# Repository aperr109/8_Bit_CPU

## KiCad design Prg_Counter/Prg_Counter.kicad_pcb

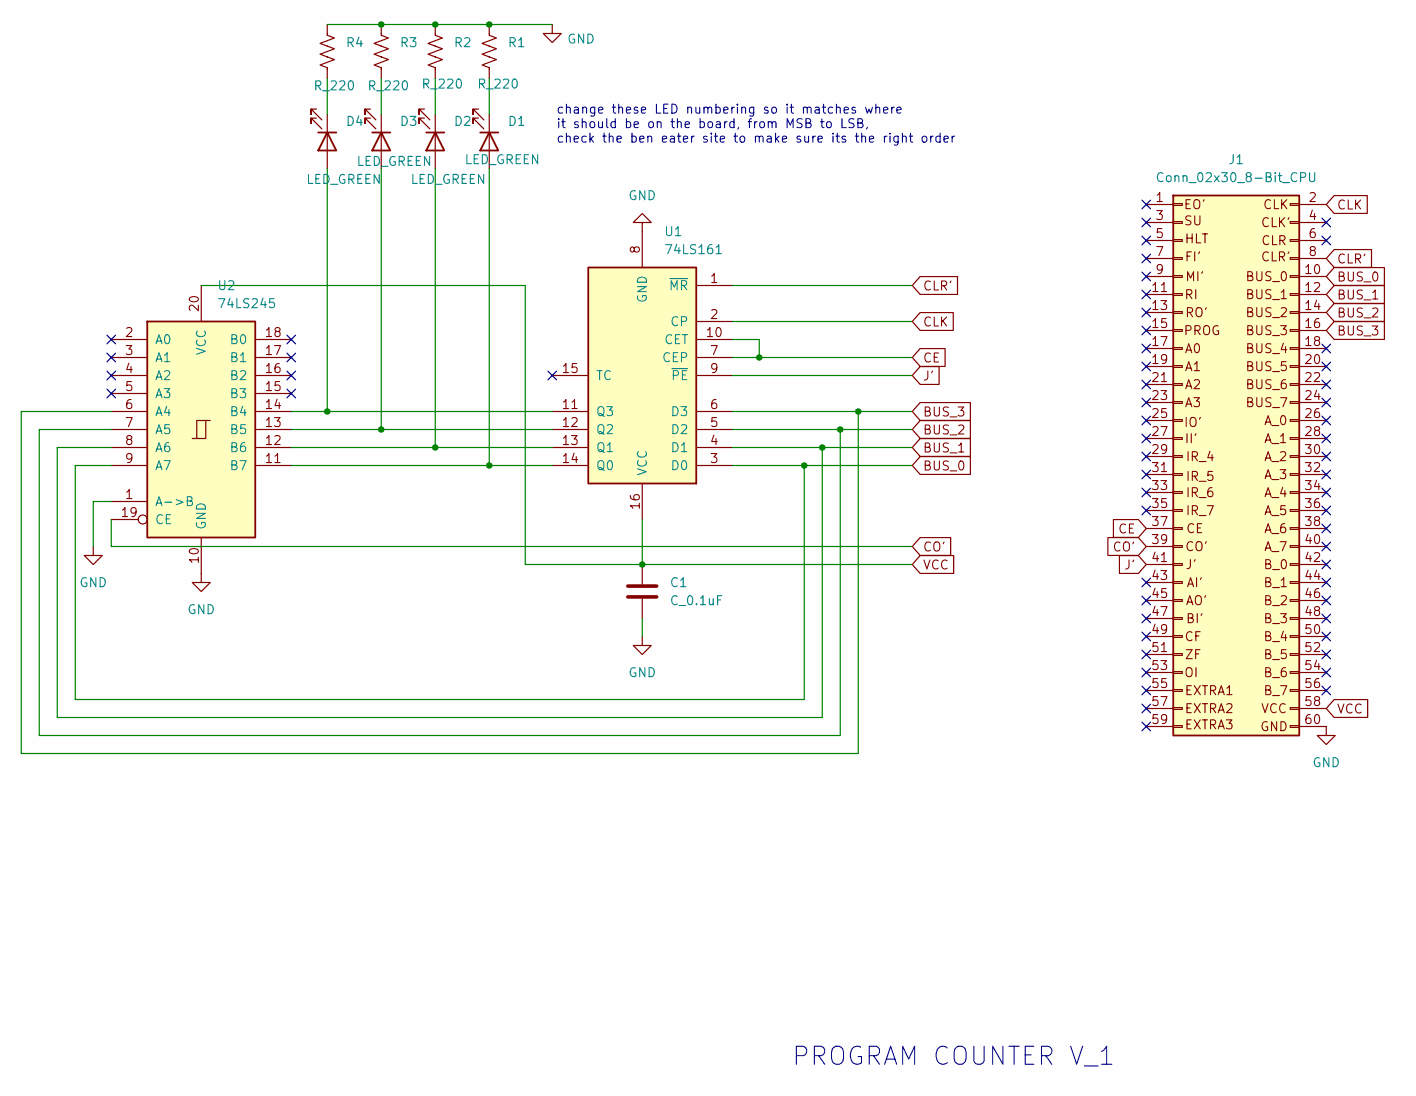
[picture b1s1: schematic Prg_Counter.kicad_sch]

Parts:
C1: C_0.1uF; C_Disc_D4.3mm_W1.9mm_P5.00mm
D1, D2, D3, D4: LED_GREEN; LED_D5.0mm
J1: Conn_02x30_8-Bit_CPU; 8_Bit_CPU_Bus_PinSocket_Bottom_Side
R1, R2, R3, R4: R_220; R_Axial_DIN0207_L6.3mm_D2.5mm_P10.16mm_Horizontal
U1: 74LS161; DIP-16_W7.62mm
U2: 74LS245; DIP-20_W7.62mm

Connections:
BUS_0: J1.10, U1.3 (D0), U2.9 (A7)
BUS_1: J1.12, U1.4 (D1), U2.8 (A6)
BUS_2: J1.14, U1.5 (D2), U2.7 (A5)
BUS_3: J1.16, U1.6 (D3), U2.6 (A4)
CE: J1.37, U1.7 (CEP), U1.10 (CET)
CLK: J1.2, U1.2 (CP)
CLR': J1.8, U1.1 (~MR)
CO': J1.39, U2.19 (CE)
GND: C1.2, J1.60, R1.1, R2.1, R3.1, R4.1, U1.8 (GND), U2.1 (A->B), U2.10 (GND)
J': J1.41, U1.9 (~PE)
unnamed: D1.2 (A), U1.14 (Q0), U2.11 (B7)
unnamed: D1.1 (K), R1.2
unnamed: D2.2 (A), U1.13 (Q1), U2.12 (B6)
unnamed: D2.1 (K), R2.2
unnamed: D3.2 (A), U1.12 (Q2), U2.13 (B5)
unnamed: D3.1 (K), R3.2
unnamed: D4.2 (A), U1.11 (Q3), U2.14 (B4)
unnamed: D4.1 (K), R4.2
VCC: C1.1, J1.58, U1.16 (VCC), U2.20 (VCC)

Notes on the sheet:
PROGRAM COUNTER V_1
change these LED numbering so it matches where it should be on the board, from MSB to LSB, check the ben eater site to make sure its the right order

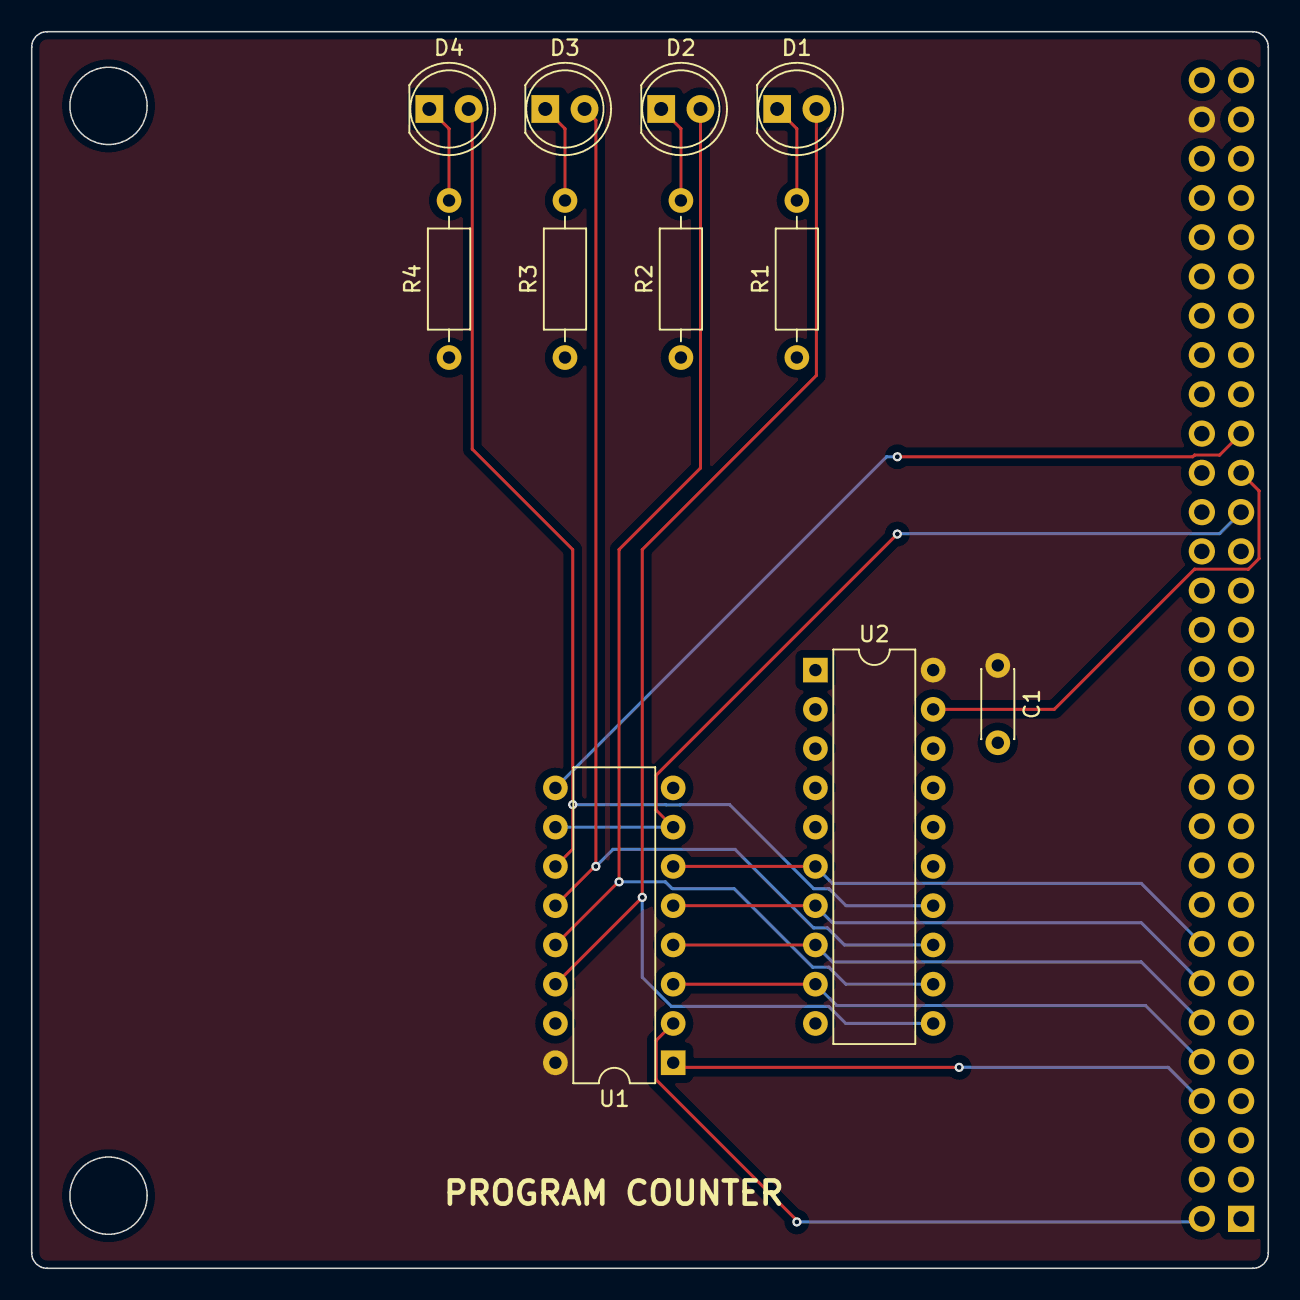
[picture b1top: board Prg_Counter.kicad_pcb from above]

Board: 2 copper layers, 80.0 x 80.0 mm, 12 parts (0 on the bottom side), 19 nets.

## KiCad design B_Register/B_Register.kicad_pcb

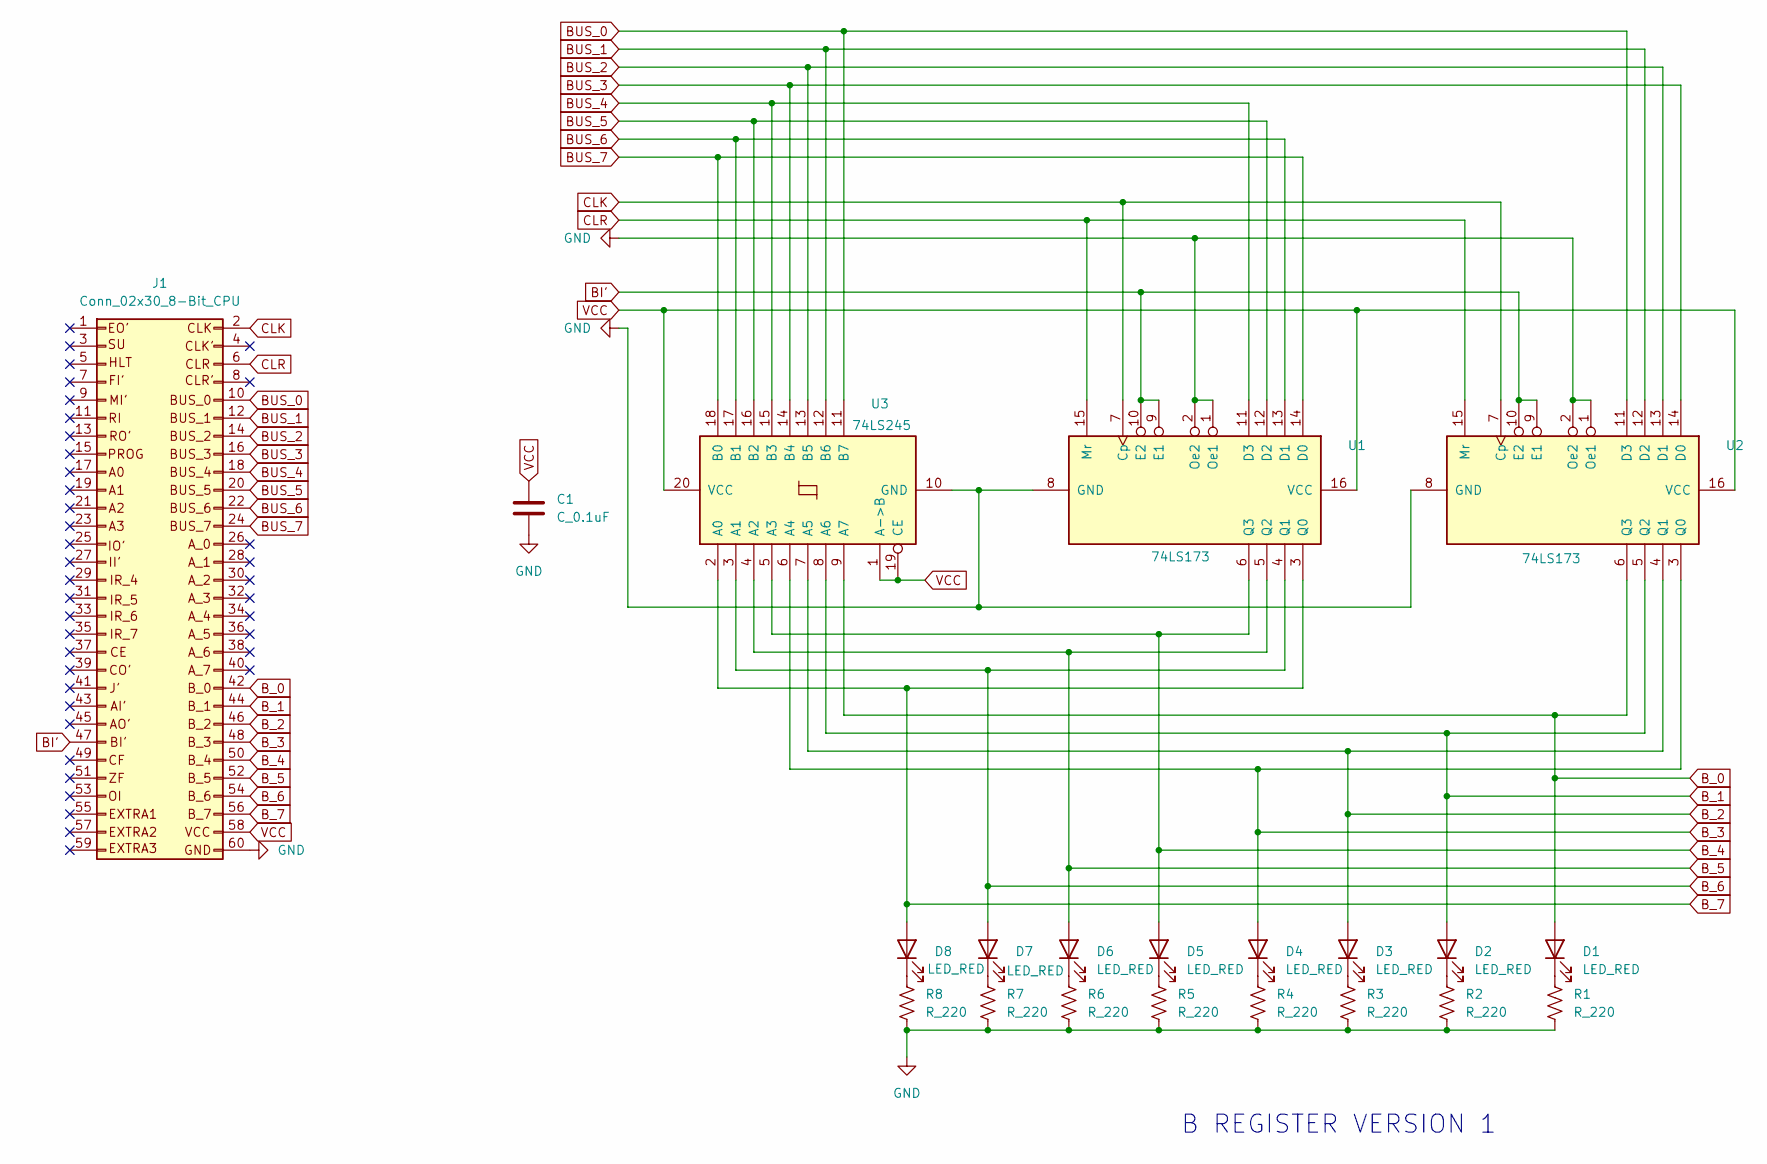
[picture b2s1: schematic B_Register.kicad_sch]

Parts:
C1: C_0.1uF; C_Disc_D4.3mm_W1.9mm_P5.00mm
D1, D2, D3, D4, D5, D6, D7, D8: LED_RED; LED_D5.0mm
J1: Conn_02x30_8-Bit_CPU; 8_Bit_CPU_Bus_PinSocket_Bottom_Side
R1, R2, R3, R4, R5, R6, R7, R8: R_220; R_Axial_DIN0207_L6.3mm_D2.5mm_P10.16mm_Horizontal
U1, U2: 74LS173; DIP-16_W7.62mm
U3: 74LS245; DIP-20_W7.62mm

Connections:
BI': J1.47, U1.9 (E1), U1.10 (E2), U2.9 (E1), U2.10 (E2)
BUS_0: J1.10, U2.11 (D3), U3.11 (B7)
BUS_1: J1.12, U2.12 (D2), U3.12 (B6)
BUS_2: J1.14, U2.13 (D1), U3.13 (B5)
BUS_3: J1.16, U2.14 (D0), U3.14 (B4)
BUS_4: J1.18, U1.11 (D3), U3.15 (B3)
BUS_5: J1.20, U1.12 (D2), U3.16 (B2)
BUS_6: J1.22, U1.13 (D1), U3.17 (B1)
BUS_7: J1.24, U1.14 (D0), U3.18 (B0)
B_0: D1.2 (A), J1.42, U2.6 (Q3), U3.9 (A7)
B_1: D2.2 (A), J1.44, U2.5 (Q2), U3.8 (A6)
B_2: D3.2 (A), J1.46, U2.4 (Q1), U3.7 (A5)
B_3: D4.2 (A), J1.48, U2.3 (Q0), U3.6 (A4)
B_4: D5.2 (A), J1.50, U1.6 (Q3), U3.5 (A3)
B_5: D6.2 (A), J1.52, U1.5 (Q2), U3.4 (A2)
B_6: D7.2 (A), J1.54, U1.4 (Q1), U3.3 (A1)
B_7: D8.2 (A), J1.56, U1.3 (Q0), U3.2 (A0)
CLK: J1.2, U1.7 (Cp), U2.7 (Cp)
CLR: J1.6, U1.15 (Mr), U2.15 (Mr)
GND: C1.2, J1.60, R1.2, R2.2, R3.2, R4.2, R5.2, R6.2, R7.2, R8.2, U1.1 (Oe1), U1.2 (Oe2), U1.8 (GND), U2.1 (Oe1), U2.2 (Oe2), U2.8 (GND), U3.10 (GND)
unnamed: D1.1 (K), R1.1
unnamed: D2.1 (K), R2.1
unnamed: D3.1 (K), R3.1
unnamed: D4.1 (K), R4.1
unnamed: D5.1 (K), R5.1
unnamed: D6.1 (K), R6.1
unnamed: D7.1 (K), R7.1
unnamed: D8.1 (K), R8.1
VCC: C1.1, J1.58, U1.16 (VCC), U2.16 (VCC), U3.1 (A->B), U3.19 (CE), U3.20 (VCC)

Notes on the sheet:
B REGISTER VERSION 1

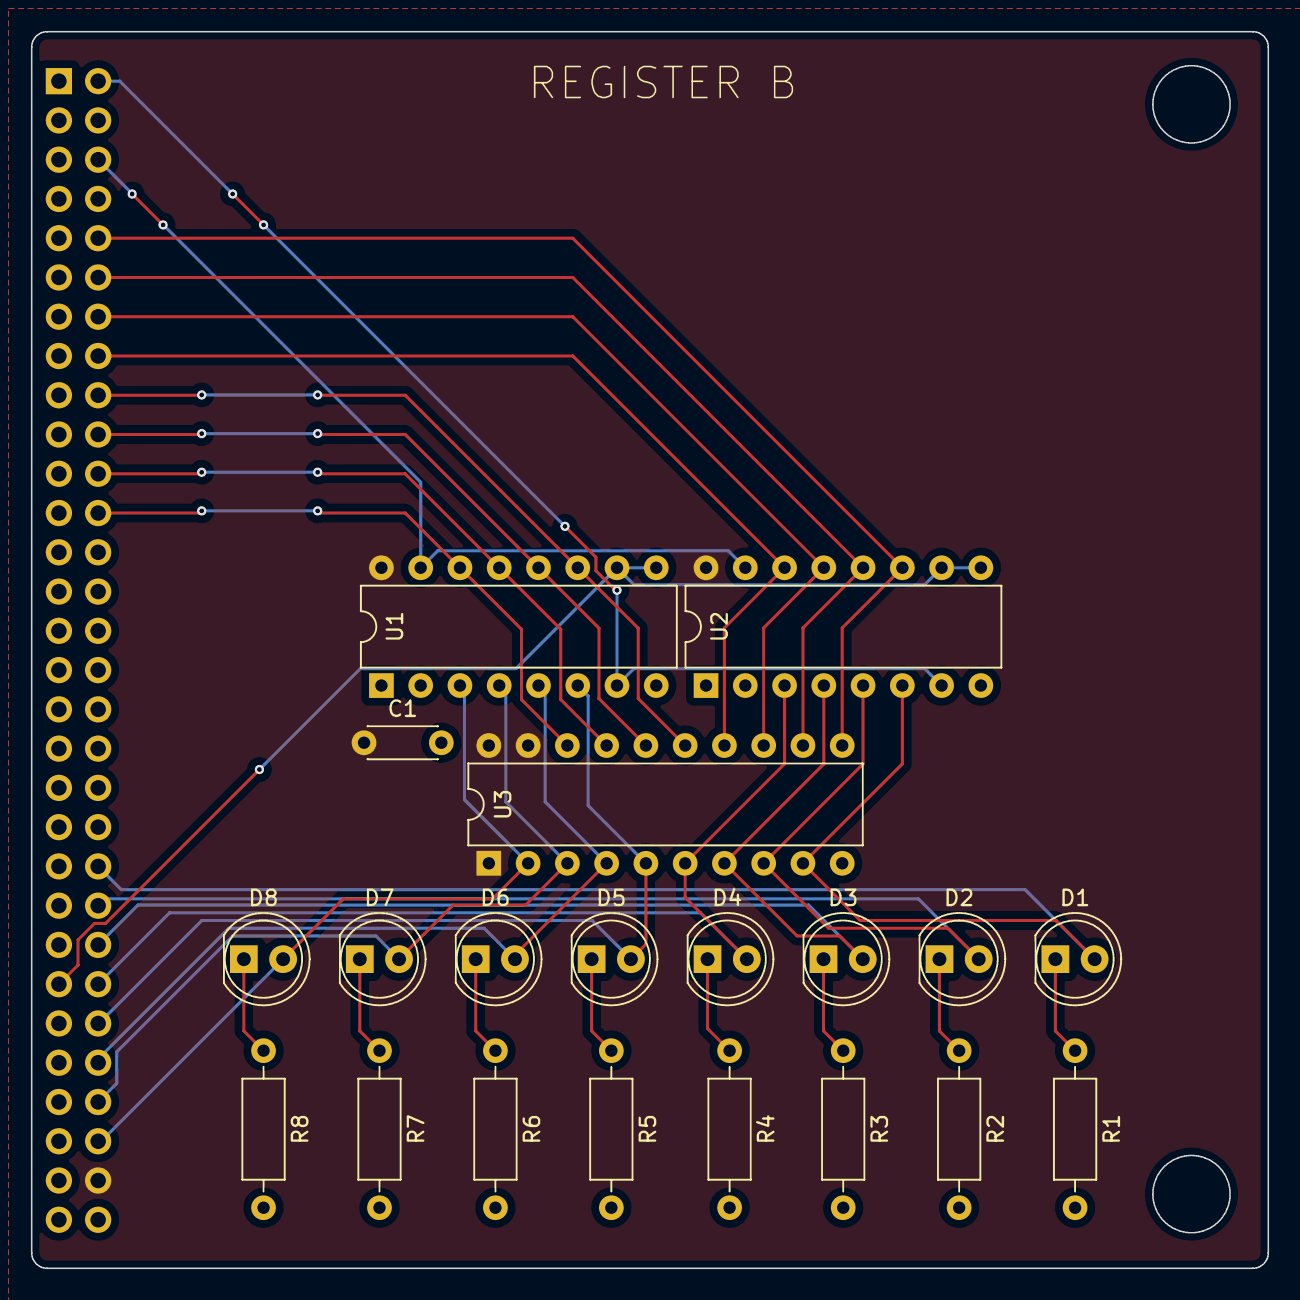
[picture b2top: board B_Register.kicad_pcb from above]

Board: 2 copper layers, 80.0 x 80.0 mm, 21 parts (0 on the bottom side), 29 nets.

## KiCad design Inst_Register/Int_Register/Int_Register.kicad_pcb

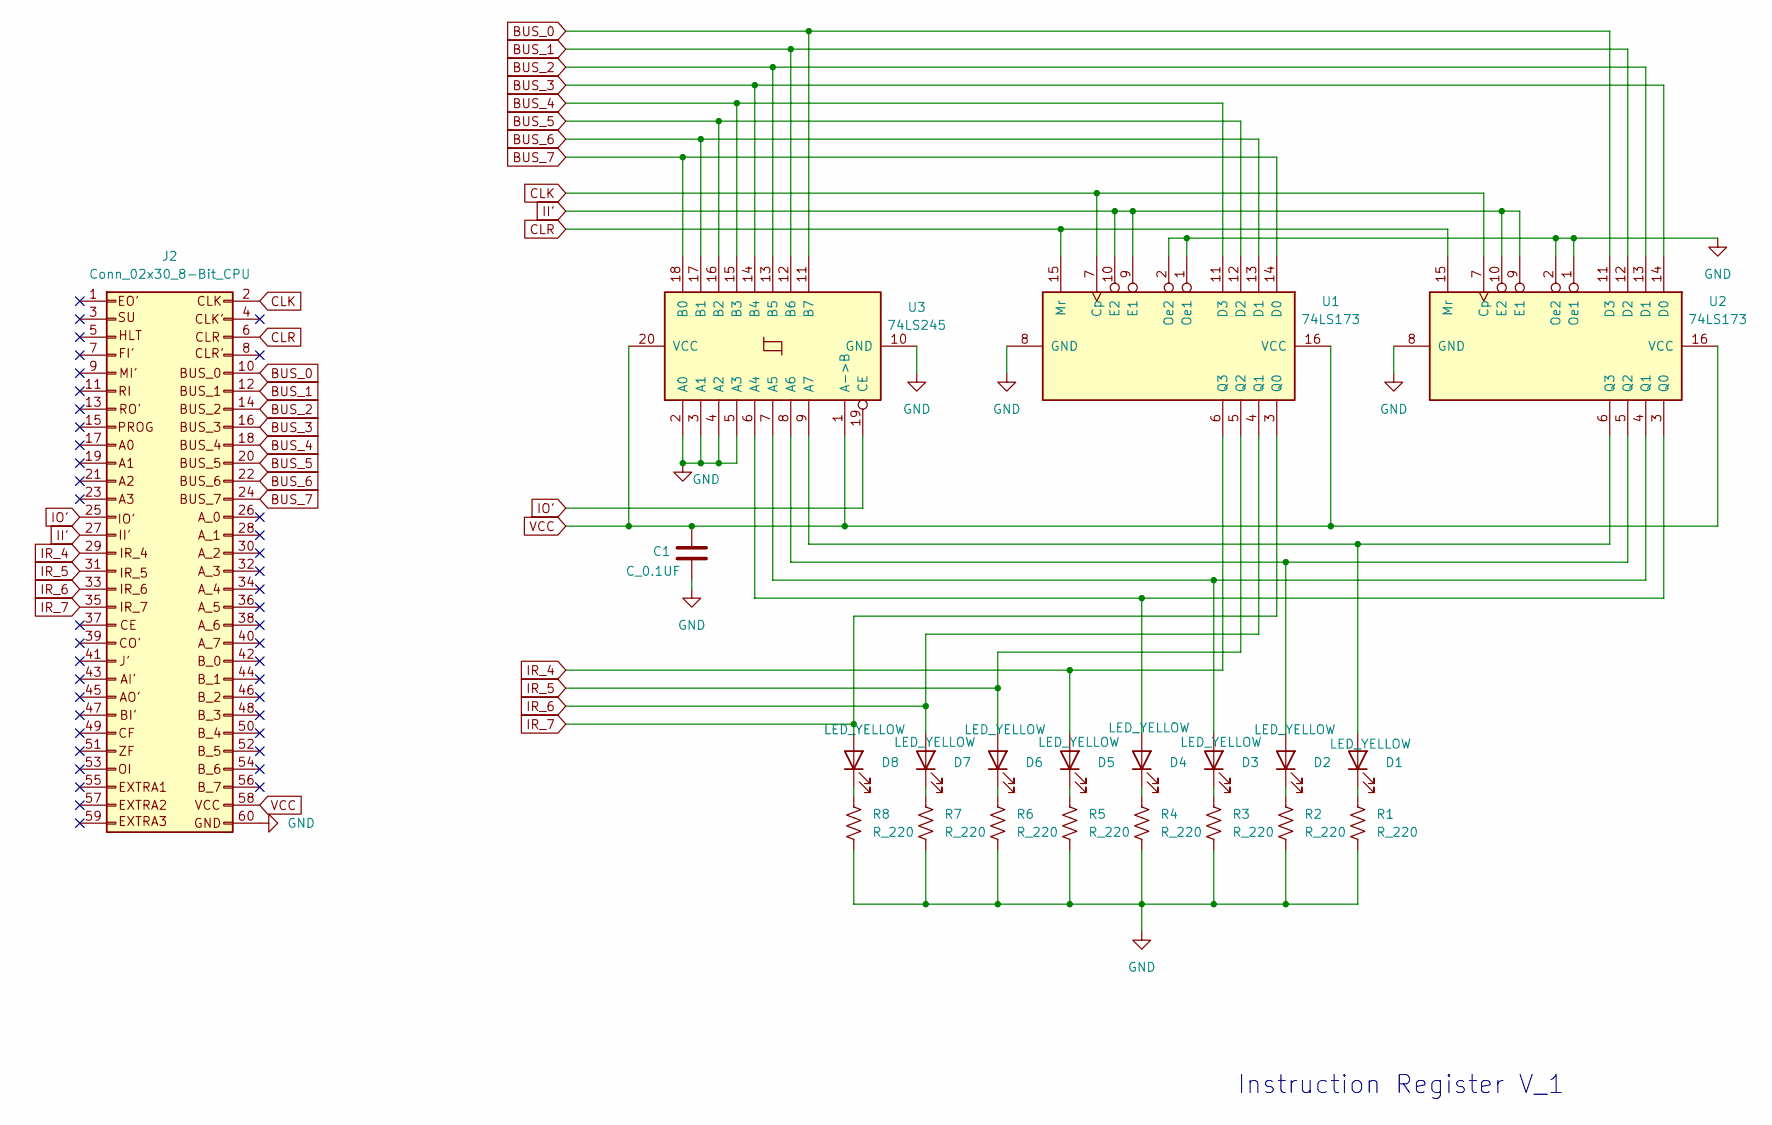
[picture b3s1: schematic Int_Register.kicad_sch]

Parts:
C1: C_0.1UF; C_Disc_D4.3mm_W1.9mm_P5.00mm
D1, D2, D3, D4, D5, D6, D7, D8: LED_YELLOW; LED_D5.0mm
J2: Conn_02x30_8-Bit_CPU; 8_Bit_CPU_Bus_PinSocket_Bottom_Side
R1, R2, R3, R4, R5, R6, R7, R8: R_220; R_Axial_DIN0207_L6.3mm_D2.5mm_P10.16mm_Horizontal
U1, U2: 74LS173; DIP-16_W7.62mm
U3: 74LS245; DIP-20_W7.62mm

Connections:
BUS_0: J2.10, U2.11 (D3), U3.11 (B7)
BUS_1: J2.12, U2.12 (D2), U3.12 (B6)
BUS_2: J2.14, U2.13 (D1), U3.13 (B5)
BUS_3: J2.16, U2.14 (D0), U3.14 (B4)
BUS_4: J2.18, U1.11 (D3), U3.15 (B3)
BUS_5: J2.20, U1.12 (D2), U3.16 (B2)
BUS_6: J2.22, U1.13 (D1), U3.17 (B1)
BUS_7: J2.24, U1.14 (D0), U3.18 (B0)
CLK: J2.2, U1.7 (Cp), U2.7 (Cp)
CLR: J2.6, U1.15 (Mr), U2.15 (Mr)
GND: C1.2, J2.60, R1.2, R2.2, R3.2, R4.2, R5.2, R6.2, R7.2, R8.2, U1.1 (Oe1), U1.2 (Oe2), U1.8 (GND), U2.1 (Oe1), U2.2 (Oe2), U2.8 (GND), U3.2 (A0), U3.3 (A1), U3.4 (A2), U3.5 (A3), U3.10 (GND)
II': J2.27, U1.9 (E1), U1.10 (E2), U2.9 (E1), U2.10 (E2)
IO': J2.25, U3.19 (CE)
IR_4: D5.2 (A), J2.29, U1.6 (Q3)
IR_5: D6.2 (A), J2.31, U1.5 (Q2)
IR_6: D7.2 (A), J2.33, U1.4 (Q1)
IR_7: D8.2 (A), J2.35, U1.3 (Q0)
unnamed: D1.2 (A), U2.6 (Q3), U3.9 (A7)
unnamed: D1.1 (K), R1.1
unnamed: D2.2 (A), U2.5 (Q2), U3.8 (A6)
unnamed: D2.1 (K), R2.1
unnamed: D3.2 (A), U2.4 (Q1), U3.7 (A5)
unnamed: D3.1 (K), R3.1
unnamed: D4.2 (A), U2.3 (Q0), U3.6 (A4)
unnamed: D4.1 (K), R4.1
unnamed: D5.1 (K), R5.1
unnamed: D6.1 (K), R6.1
unnamed: D7.1 (K), R7.1
unnamed: D8.1 (K), R8.1
VCC: C1.1, J2.58, U1.16 (VCC), U2.16 (VCC), U3.1 (A->B), U3.20 (VCC)

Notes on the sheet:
Instruction Register V_1

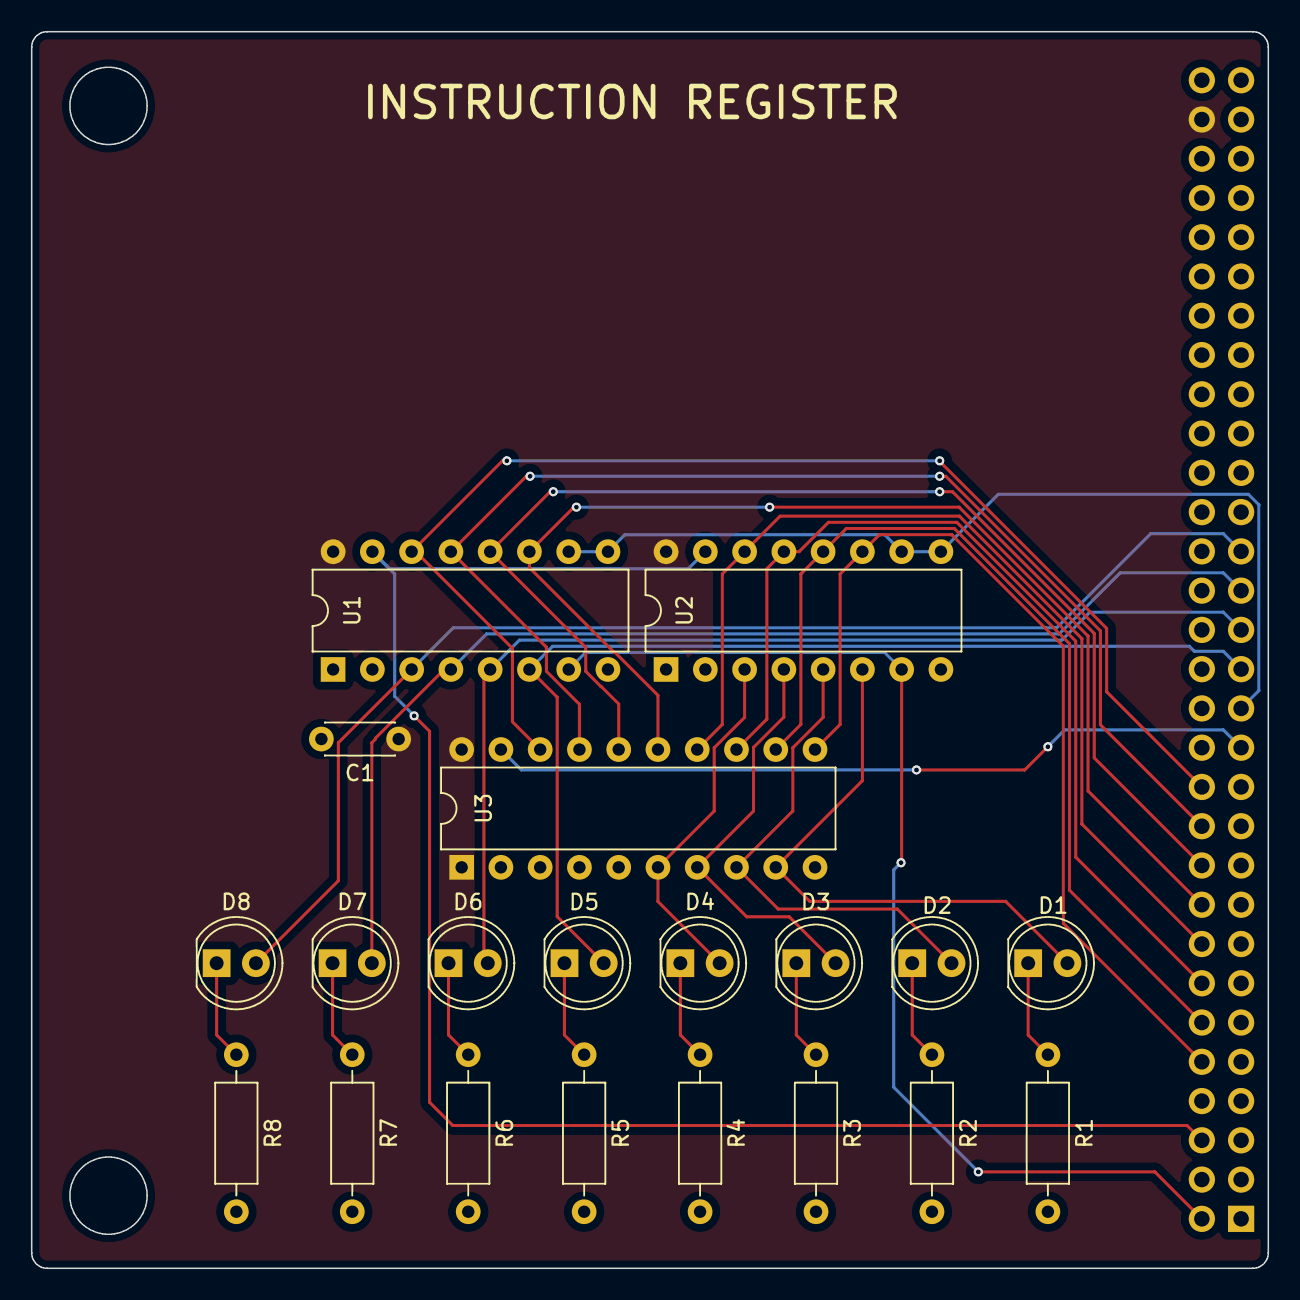
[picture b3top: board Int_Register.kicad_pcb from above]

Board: 2 copper layers, 80.0 x 80.0 mm, 21 parts (0 on the bottom side), 30 nets.

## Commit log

2025-07-20 uploaded all current versions of the board files and added proper gitignore
